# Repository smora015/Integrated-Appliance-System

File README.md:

# Integrated-Appliance-System
##### Controllers for an Energy Efficient, Sustainable Appliance System.

The Integrated Appliance System is a Senior Design, or capstone project for the Department of Chemical & Environmental Engineering for UC Riverside, under the advisory of Dr. Kawai Tam. We aim to draft, design, and potentially market an energy combination of appliances that cut your electricity bill substantially. It's common knowledge that appliances such as washers and dryers in typical residential homes are among the highest in terms of energy consumption. We're an interdisciplinary team that consists of Chemical, Environmental, Mechanical, and Computer Engineering majors. In a nut shell, the design utilizes solar thermal energy to heat up clothes, and taking the surplus energy to be routed into a water heater or into a home as warm air for heating, thus replacing a clothes dryer, water heater, and space heater. Being pretty savvy in embedded systems, I was reached out to implement a control system for the appliances. 

### Subsystems

##### IAS-PCB
Collection of Eagle PCB CAD files that contain prototype/production-ready schematic and board layouts for the IAS.

##### Integrated Appliance System
Contains the Atmel Project source for the ATmega1284-PU work.

##### Raspberry-Pi-Logger
Contains logic for a temporary method of controlling the IAS, utilizing startup scripts to log temperature and humidity data.

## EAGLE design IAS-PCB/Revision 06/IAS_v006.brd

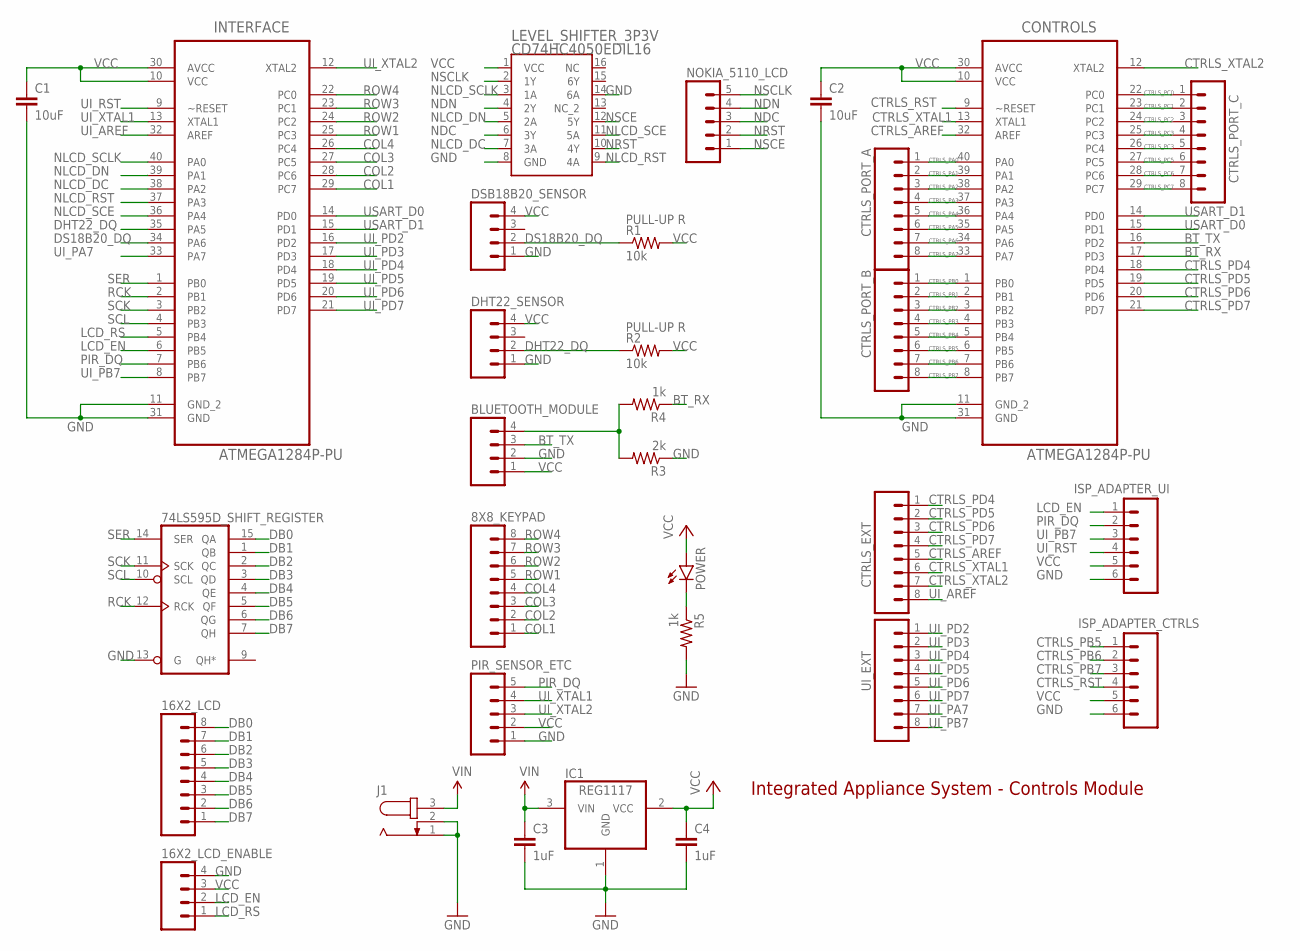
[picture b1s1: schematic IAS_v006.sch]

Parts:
8X8_KEYPAD, 16X2_LCD: M08; 1X08_ROUND
16X2_LCD_ENABLE: M04NO_SILK_ALL_ROUND; 1X04_NO_SILK_ALL_ROUND
74LS595D_SHIFT_REGISTER: 74LS595N; DIL16; MPN SN74LS595D
BLUETOOTH_MODULE: M04NO_SILK_ALL_ROUND; 1X04_NO_SILK_ALL_ROUND
C1, C2: 10uF; 1206
C3, C4: 1uF; 1206
CONTROLS: ATMEGA1284P-PU; DIP254P1524X483-40
CTRLS_EXT: M08; 1X08_ROUND
CTRLS_PORT_A: M08; 1X08_ROUND
CTRLS_PORT_B: M08; 1X08_ROUND
CTRLS_PORT_C: M08; 1X08_ROUND
DHT22_SENSOR: M04NO_SILK_ALL_ROUND; 1X04_NO_SILK_ALL_ROUND
DSB18B20_SENSOR: M04NO_SILK_ALL_ROUND; 1X04_NO_SILK_ALL_ROUND
IC1: REG1117; SOT223
INTERFACE: ATMEGA1284P-PU; DIP254P1524X483-40
ISP_ADAPTER_CTRLS: M06SILK_FEMALE_PTH; 1X06
ISP_ADAPTER_UI: M06SILK_FEMALE_PTH; 1X06
J1: JACK-PLUG0; SPC4077
LEVEL_SHIFTER_3P3V: CD74HC4050EDIL16; DIL16
NOKIA_5110_LCD: M05PTH; 1X05
PIR_SENSOR_ETC: M05PTH; 1X05
POWER: LED3MM
R1, R2: 10k; 1206
R3: 2k; 1206
R4, R5: 1k; 1206
UI_EXT: M08; 1X08_ROUND

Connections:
BT_RX: CONTROLS.17 (PD3), R4.1
BT_TX: BLUETOOTH_MODULE.3, CONTROLS.16 (PD2)
COL1: 8X8_KEYPAD.1, INTERFACE.29 (PC7)
COL2: 8X8_KEYPAD.2, INTERFACE.28 (PC6)
COL3: 8X8_KEYPAD.3, INTERFACE.27 (PC5)
COL4: 8X8_KEYPAD.4, INTERFACE.26 (PC4)
CTRLS_AREF: CONTROLS.32 (AREF), CTRLS_EXT.5
CTRLS_PA0: CONTROLS.40 (PA0), CTRLS_PORT_A.1
CTRLS_PA1: CONTROLS.39 (PA1), CTRLS_PORT_A.2
CTRLS_PA2: CONTROLS.38 (PA2), CTRLS_PORT_A.3
CTRLS_PA3: CONTROLS.37 (PA3), CTRLS_PORT_A.4
CTRLS_PA4: CONTROLS.36 (PA4), CTRLS_PORT_A.5
CTRLS_PA5: CONTROLS.35 (PA5), CTRLS_PORT_A.6
CTRLS_PA6: CONTROLS.34 (PA6), CTRLS_PORT_A.7
CTRLS_PA7: CONTROLS.33 (PA7), CTRLS_PORT_A.8
CTRLS_PB0: CONTROLS.1 (PB0), CTRLS_PORT_B.1
CTRLS_PB1: CONTROLS.2 (PB1), CTRLS_PORT_B.2
CTRLS_PB2: CONTROLS.3 (PB2), CTRLS_PORT_B.3
CTRLS_PB3: CONTROLS.4 (PB3), CTRLS_PORT_B.4
CTRLS_PB4: CONTROLS.5 (PB4), CTRLS_PORT_B.5
CTRLS_PB5: CONTROLS.6 (PB5), CTRLS_PORT_B.6, ISP_ADAPTER_CTRLS.1
CTRLS_PB6: CONTROLS.7 (PB6), CTRLS_PORT_B.7, ISP_ADAPTER_CTRLS.2
CTRLS_PB7: CONTROLS.8 (PB7), CTRLS_PORT_B.8, ISP_ADAPTER_CTRLS.3
CTRLS_PC0: CONTROLS.22 (PC0), CTRLS_PORT_C.1
CTRLS_PC1: CONTROLS.23 (PC1), CTRLS_PORT_C.2
CTRLS_PC2: CONTROLS.24 (PC2), CTRLS_PORT_C.3
CTRLS_PC3: CONTROLS.25 (PC3), CTRLS_PORT_C.4
CTRLS_PC4: CONTROLS.26 (PC4), CTRLS_PORT_C.5
CTRLS_PC5: CONTROLS.27 (PC5), CTRLS_PORT_C.6
CTRLS_PC6: CONTROLS.28 (PC6), CTRLS_PORT_C.7
CTRLS_PC7: CONTROLS.29 (PC7), CTRLS_PORT_C.8
CTRLS_PD4: CONTROLS.18 (PD4), CTRLS_EXT.1
CTRLS_PD5: CONTROLS.19 (PD5), CTRLS_EXT.2
CTRLS_PD6: CONTROLS.20 (PD6), CTRLS_EXT.3
CTRLS_PD7: CONTROLS.21 (PD7), CTRLS_EXT.4
CTRLS_RST: CONTROLS.9 (~RESET), ISP_ADAPTER_CTRLS.4
CTRLS_XTAL1: CONTROLS.13 (XTAL1), CTRLS_EXT.6
CTRLS_XTAL2: CONTROLS.12 (XTAL2), CTRLS_EXT.7
DB0: 16X2_LCD.8, 74LS595D_SHIFT_REGISTER.15 (QA)
DB1: 16X2_LCD.7, 74LS595D_SHIFT_REGISTER.1 (QB)
DB2: 16X2_LCD.6, 74LS595D_SHIFT_REGISTER.2 (QC)
DB3: 16X2_LCD.5, 74LS595D_SHIFT_REGISTER.3 (QD)
DB4: 16X2_LCD.4, 74LS595D_SHIFT_REGISTER.4 (QE)
DB5: 16X2_LCD.3, 74LS595D_SHIFT_REGISTER.5 (QF)
DB6: 16X2_LCD.2, 74LS595D_SHIFT_REGISTER.6 (QG)
DB7: 16X2_LCD.1, 74LS595D_SHIFT_REGISTER.7 (QH)
DHT22_DQ: DHT22_SENSOR.2, INTERFACE.35 (PA5), R2.1
DS18B20_DQ: DSB18B20_SENSOR.2, INTERFACE.34 (PA6), R1.1
GND: 16X2_LCD_ENABLE.4, 74LS595D_SHIFT_REGISTER.8 (GND), 74LS595D_SHIFT_REGISTER.13 (G), BLUETOOTH_MODULE.2, C1.2, C2.2, C3.2, C4.2, CONTROLS.11 (GND_2), CONTROLS.31 (GND), DHT22_SENSOR.1, DSB18B20_SENSOR.1, IC1.1 (GND), INTERFACE.11 (GND_2), INTERFACE.31 (GND), ISP_ADAPTER_CTRLS.6, ISP_ADAPTER_UI.6, J1.1, J1.2, LEVEL_SHIFTER_3P3V.8 (GND), LEVEL_SHIFTER_3P3V.14 (6A), PIR_SENSOR_ETC.1, R3.1, R5.2
LCD_EN: 16X2_LCD_ENABLE.2, INTERFACE.6 (PB5), ISP_ADAPTER_UI.1
LCD_RS: 16X2_LCD_ENABLE.1, INTERFACE.5 (PB4)
unnamed: POWER.K (C), R5.1
unnamed: BLUETOOTH_MODULE.4, R3.2, R4.2
NDC: LEVEL_SHIFTER_3P3V.6 (3Y), NOKIA_5110_LCD.3
NDN: LEVEL_SHIFTER_3P3V.4 (2Y), NOKIA_5110_LCD.4
NLCD_DC: INTERFACE.38 (PA2), LEVEL_SHIFTER_3P3V.7 (3A)
NLCD_DN: INTERFACE.39 (PA1), LEVEL_SHIFTER_3P3V.5 (2A)
NLCD_RST: INTERFACE.37 (PA3), LEVEL_SHIFTER_3P3V.9 (4A)
NLCD_SCE: INTERFACE.36 (PA4), LEVEL_SHIFTER_3P3V.11 (5A)
NLCD_SCLK: INTERFACE.40 (PA0), LEVEL_SHIFTER_3P3V.3 (1A)
NRST: LEVEL_SHIFTER_3P3V.10 (4Y), NOKIA_5110_LCD.2
NSCE: LEVEL_SHIFTER_3P3V.12 (5Y), NOKIA_5110_LCD.1
NSCLK: LEVEL_SHIFTER_3P3V.2 (1Y), NOKIA_5110_LCD.5
PIR_DQ: INTERFACE.7 (PB6), ISP_ADAPTER_UI.2, PIR_SENSOR_ETC.5
RCK: 74LS595D_SHIFT_REGISTER.12 (RCK), INTERFACE.2 (PB1)
ROW1: 8X8_KEYPAD.5, INTERFACE.25 (PC3)
ROW2: 8X8_KEYPAD.6, INTERFACE.24 (PC2)
ROW3: 8X8_KEYPAD.7, INTERFACE.23 (PC1)
ROW4: 8X8_KEYPAD.8, INTERFACE.22 (PC0)
SCK: 74LS595D_SHIFT_REGISTER.11 (SCK), INTERFACE.3 (PB2)
SCL: 74LS595D_SHIFT_REGISTER.10 (SCL), INTERFACE.4 (PB3)
SER: 74LS595D_SHIFT_REGISTER.14 (SER), INTERFACE.1 (PB0)
UI_AREF: CTRLS_EXT.8, INTERFACE.32 (AREF)
UI_PA7: INTERFACE.33 (PA7), UI_EXT.7
UI_PB7: INTERFACE.8 (PB7), ISP_ADAPTER_UI.3, UI_EXT.8
UI_PD2: INTERFACE.16 (PD2), UI_EXT.1
UI_PD3: INTERFACE.17 (PD3), UI_EXT.2
UI_PD4: INTERFACE.18 (PD4), UI_EXT.3
UI_PD5: INTERFACE.19 (PD5), UI_EXT.4
UI_PD6: INTERFACE.20 (PD6), UI_EXT.5
UI_PD7: INTERFACE.21 (PD7), UI_EXT.6
UI_RST: INTERFACE.9 (~RESET), ISP_ADAPTER_UI.4
UI_XTAL1: INTERFACE.13 (XTAL1), PIR_SENSOR_ETC.4
UI_XTAL2: INTERFACE.12 (XTAL2), PIR_SENSOR_ETC.3
USART_D0: CONTROLS.15 (PD1), INTERFACE.14 (PD0)
USART_D1: CONTROLS.14 (PD0), INTERFACE.15 (PD1)
VCC: 16X2_LCD_ENABLE.3, 74LS595D_SHIFT_REGISTER.16 (VCC), BLUETOOTH_MODULE.1, C1.1, C2.1, C4.1, CONTROLS.10 (VCC), CONTROLS.30 (AVCC), DHT22_SENSOR.4, DSB18B20_SENSOR.4, IC1.2 (VCC), INTERFACE.10 (VCC), INTERFACE.30 (AVCC), ISP_ADAPTER_CTRLS.5, ISP_ADAPTER_UI.5, LEVEL_SHIFTER_3P3V.1 (VCC), PIR_SENSOR_ETC.2, POWER.A, R1.2, R2.2
VIN: C3.1, IC1.3 (VIN), J1.3

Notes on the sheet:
PULL-UP R
Integrated Appliance System - Controls Module

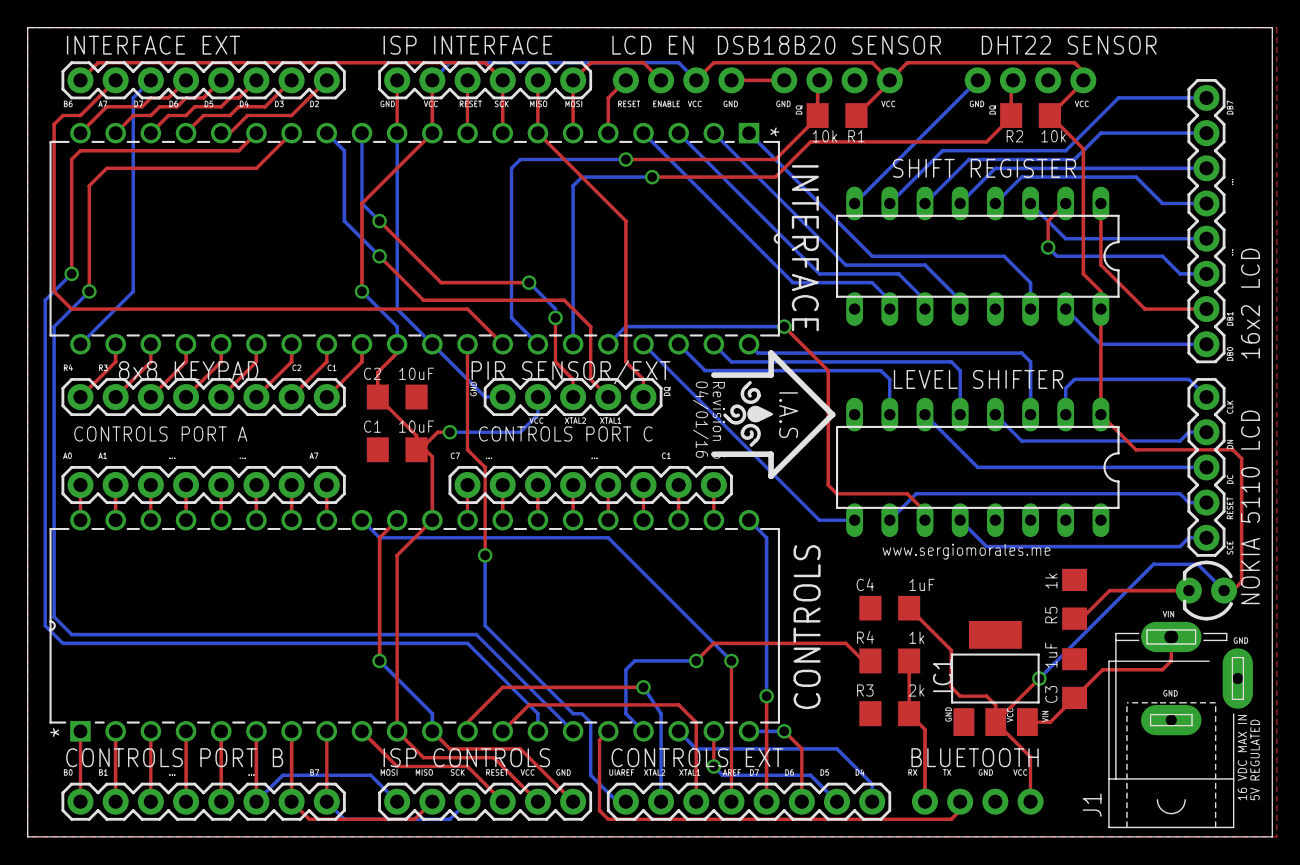
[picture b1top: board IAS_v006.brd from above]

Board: 2 copper layers, 89.8 x 58.4 mm, 31 parts (0 on the bottom side), 88 nets.

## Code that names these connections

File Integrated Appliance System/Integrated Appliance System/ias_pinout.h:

/*
 * ias_pinout.h
 *
 * Created: 10/12/2015 9:33:00 PM
 *  Author: Sergio
 *
 *  Description: Defines the pinout for all ports 
 */ 



#ifndef IAS_PINOUT_H_
#define IAS_PINOUT_H_
    
    #include <avr/io.h>
    
    /* ============== Communication ============== */

    // 4x4 Keypad { keypad.h }
    #define KEYPADPORT PORTC
    #define KEYPADPIN  PINC
    #define ROW1 3
    #define ROW2 2
    #define ROW3 1
    #define ROW4 0
    #define COL1 7
    #define COL2 6
    #define COL3 5
    #define COL4 4

    // Shift Register { shift_reg.h }
    #define SHIFT_PORT PORTB
    #define SER_PIN   0
    #define RCLK_PIN  1
    #define SRCLK_PIN 2
    #define SRCLR_PIN 3

    /* ============== Sensors ============== */

    // DHT22 Temp/Humidity Sensor { dht22.h }
    #define DHT_DDR DDRA
    #define DHT_PORT PORTA
    #define DHT_PIN PINA
    #define DHT_INPUTPIN 5

    // DS18B20 Temperature Probe { ds18b20.h }
    #define DS18B20_PORT PORTA
    #define DS18B20_DDR  DDRA
    #define DS18B20_PIN  PINA
    #define DS18B20_DQ   6
    
    // PIR Motion Sensor { pir.h }
    #define PIR_DDR  DDRB
    #define PIR_READ PINB
    #define PIR_PIN  6

    /* ============== Display ============== */

    // 16x2 LUMEX LCD { lumex_lcd.h }
    //#define DATA_BUS PORTB          // port connected to pins 7-14 of LCD display | WE NOW USE SHIFT REGISTERS ON DEFINED PINS
    #define CONTROL_BUS PORTB	      // port connected to pins 4 and 6 of LCD disp.
    #define RS 4			          // pin number of uC connected to pin 4 of LCD disp.
    #define E 5			              // pin number of uC connected to pin 6 of LCD disp.

    // NOKIA 84x48 PCD8544 LCD { pcd8544.h }
    #define LCD_PORT            PORTA
    #define LCD_SCE_HI			LCD_PORT |= (1<<4)
    #define LCD_SCE_LO			LCD_PORT &= ~(1<<4)
    #define LCD_RST_HI			LCD_PORT |= (1<<3)
    #define LCD_RST_LO			LCD_PORT &= ~(1<<3)
    #define LCD_DC_HI			LCD_PORT |= (1<<2)
    #define LCD_DC_LO			LCD_PORT &= ~(1<<2)
    #define LCD_DN_HI			LCD_PORT |= (1<<1)
    #define LCD_DN_LO			LCD_PORT &= ~(1<<1)
    #define LCD_SCLK_HI			LCD_PORT |= (1<<0)
    #define LCD_SCLK_LO			LCD_PORT &= ~(1<<0)
    //#define LCD_BACKLIGHT_HI	LCD_PORT |= (1<<5)   // Optional
    //#define LCD_BACKLIGHT_LO	LCD_PORT &= ~(1<<5)  // Optional
    
    #define LCD_C 0 // Command
    #define LCD_D 1 // Data

    #define LCD_WIDTH	84
    #define LCD_HEIGHT	48

#endif /* IAS_PINOUT_H_ */

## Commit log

2014-12-16 :lollipop: Added .gitattributes & .gitignore files
2015-08-17 Initial basic DHT22 interfacing in C
2015-08-17 Init DHT22 C interface
2015-11-16 Added PCB CAD files and reorganized
    IAS PCB revision .05 finished. Started working on Atmel project as well.
2016-04-29 Revive Atmel Studio Project & Update RPI Code
    Update code to work with IAS Revision 06 PCB.
    Update Raspberry Pi DHT 22 Logger code.

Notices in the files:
parts and their libraries:
SparkFun-Connectors: Licensing: Creative Commons ShareAlike 4.0 International - https://creativecommons.org/licenses/by-sa/4.0
COPYRIGHT: Copyright (C) 2015 Accelerated Designs. All rights reserved
